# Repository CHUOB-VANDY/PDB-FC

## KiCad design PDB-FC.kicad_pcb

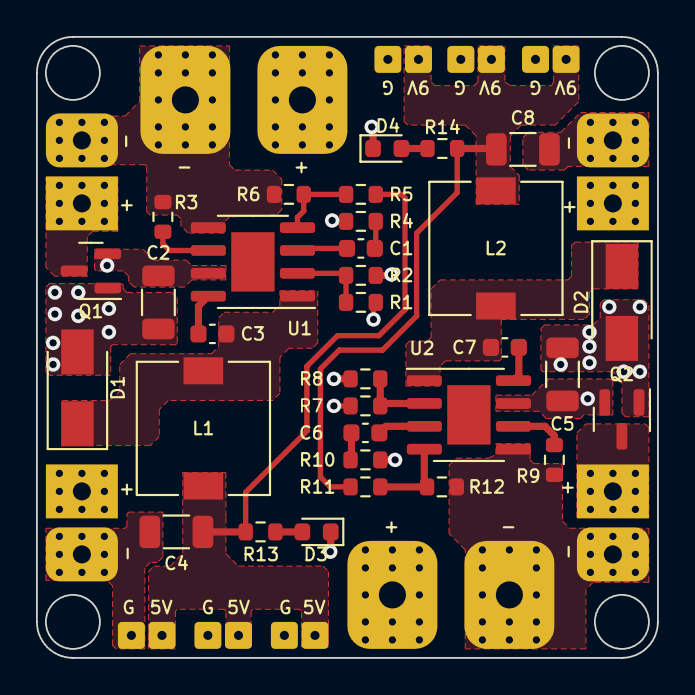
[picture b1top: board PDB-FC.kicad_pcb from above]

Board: 4 copper layers, 34.5 x 34.5 mm, 44 parts (0 on the bottom side), 22 nets.

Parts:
C1, C6: 150pF; C_0603_1608Metric
C2, C5: 10uF; C_1206_3216Metric
C3, C7: 100nF; C_0603_1608Metric
C4, C8: 22uF; C_1206_3216Metric
D1, D2: SS34; D_SMA
D3, D4: LEDR; LED_0603_1608Metric
J1, J12: Conn_01x02; PDB_6mm
J2, J3, J4, J5: Conn_01x02; PDB_Pad01x02
J6, J7, J8, J9, J10, J11: Conn_01x02; ConPadx02-1.5mm
L1, L2: 22uH; L_7.3x7.3_H4.5
Q1, Q2: AO3401A; SOT-23
R1, R3, R4, R7, R9, R10: 100k; R_0603_1608Metric
R2, R6, R8: 24k; R_0603_1608Metric
R5: 126k; R_0603_1608Metric
R11: 400k; R_0603_1608Metric
R12: 39k; R_0603_1608Metric
R13: 330R; R_0603_1608Metric
R14: 1k; R_0603_1608Metric
U1, U2: MP1584; SOIC-8-1EP_3.9x4.9mm_P1.27mm_EP2.41x3.3mm

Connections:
+5V: C4.1, J9.2, J10.2, J11.2, L1.2, R5.1, R13.1
+9V: C8.1, J6.2, J7.2, J8.2, L2.2, R11.1, R14.1
/BST: C3.1, U1.8 (BST)
/BST_9: C7.1, U2.8 (BST)
/COMP: C1.1, U1.3 (COMP)
/COMP_9: C6.1, U2.3 (COMP)
/EN: R1.2, R2.1, U1.2 (EN)
/EN_9: R7.2, R8.1, U2.2 (EN)
/FB: R5.2, R6.1, U1.4 (FB)
/FB_9: R11.2, R12.1, U2.4 (FB)
/FREQ: R3.1, U1.6 (FREQ)
/FREQ_9: R9.1, U2.6 (FREQ)
/SW: C3.2, D1.1 (K), L1.1, U1.1 (SW)
/SW_9: C7.2, D2.1 (K), L2.1, U2.1 (SW)
/VIN: C2.1, Q1.2 (S), R1.1, U1.7 (VIN)
/VIN_9: C5.1, Q2.2 (S), R7.1, U2.7 (VIN)
GND: C2.2, C4.2, C5.2, C8.2, D1.2 (A), D2.2 (A), D3.1 (K), D4.1 (K), J1.1, J2.1, J3.1, J4.1, J5.1, J6.1, J7.1, J8.1, J9.1, J10.1, J11.1, J12.1, Q1.1 (G), Q2.1 (G), R2.2, R3.2, R4.2, R6.2, R8.2, R9.2, R10.2, R12.2, U1.5 (GND), U2.5 (GND)
unnamed: C1.2, R4.1
unnamed: C6.2, R10.1
unnamed: D3.2 (A), R13.2
unnamed: D4.2 (A), R14.2
VCC: J1.2, J2.2, J3.2, J4.2, J5.2, J12.2, Q1.3 (D), Q2.3 (D)

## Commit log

2022-09-29 add logo
